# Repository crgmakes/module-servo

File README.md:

# Servo Module

All the source files for the servo module hardware.

# Software 

You will need [KiCad](https://kicad.org) to view and edit this design. Click [here](https://www.kicad.org/download/) to download.

You will also need all the associated libraries and models to drive the design if you want to make changes or view the 3D rendering:

https://github.com/crgmakes/kicad-library.git

Kicad MUST be configured properly to use all the files in this repo. Once you have Kicad installed, under Preferences->Configure Paths..., make the following entries:

1. KICAD_USER_DIR -> set to the root location of where you placed the above repository.
2. KICAD_USER_LIBRARY = ${KICAD_USER_DIR}/Library
3. KICAD_USER_MODEL_DIR = ${KICAD_USER_LIBRARY}/models
4. KICAD_USER_TEMPLATE_DIR = ${KICAD_USER_LIBRARY}/templates	

Kicad will operate mostly normally if these are not set properly. You will notice an issue when you view the PCB in 3D mode.

***NOTE***: after makeing a release build in git, if your rendered 3D images are missing components, ensure the path to EVERY component model is set to ${KICAD_USER_MODEL_DIR}/<model name>.

Kicad sometimes replaces the variable with an expansion and that FAILS during the build process because the expanded variable is local and does not match the build environment.

---

THE DESIGN IS PROVIDED "AS IS" AND THE AUTHOR DISCLAIMS ALL WARRANTIES WITH REGARD TO THIS DESIGN INCLUDING ALL IMPLIED WARRANTIES OF MERCHANTABILITY AND FITNESS. IN NO EVENT SHALL THE AUTHOR BE LIABLE FOR ANY SPECIAL, DIRECT, INDIRECT, OR CONSEQUENTIAL DAMAGES OR ANY DAMAGES WHATSOEVER RESULTING FROM LOSS OF USE, DATA OR PROFITS, WHETHER IN AN ACTION OF CONTRACT, NEGLIGENCE OR OTHER TORTIOUS ACTION, ARISING OUT OF OR IN CONNECTION WITH THE USE OR PERFORMANCE OF THIS DESIGN.

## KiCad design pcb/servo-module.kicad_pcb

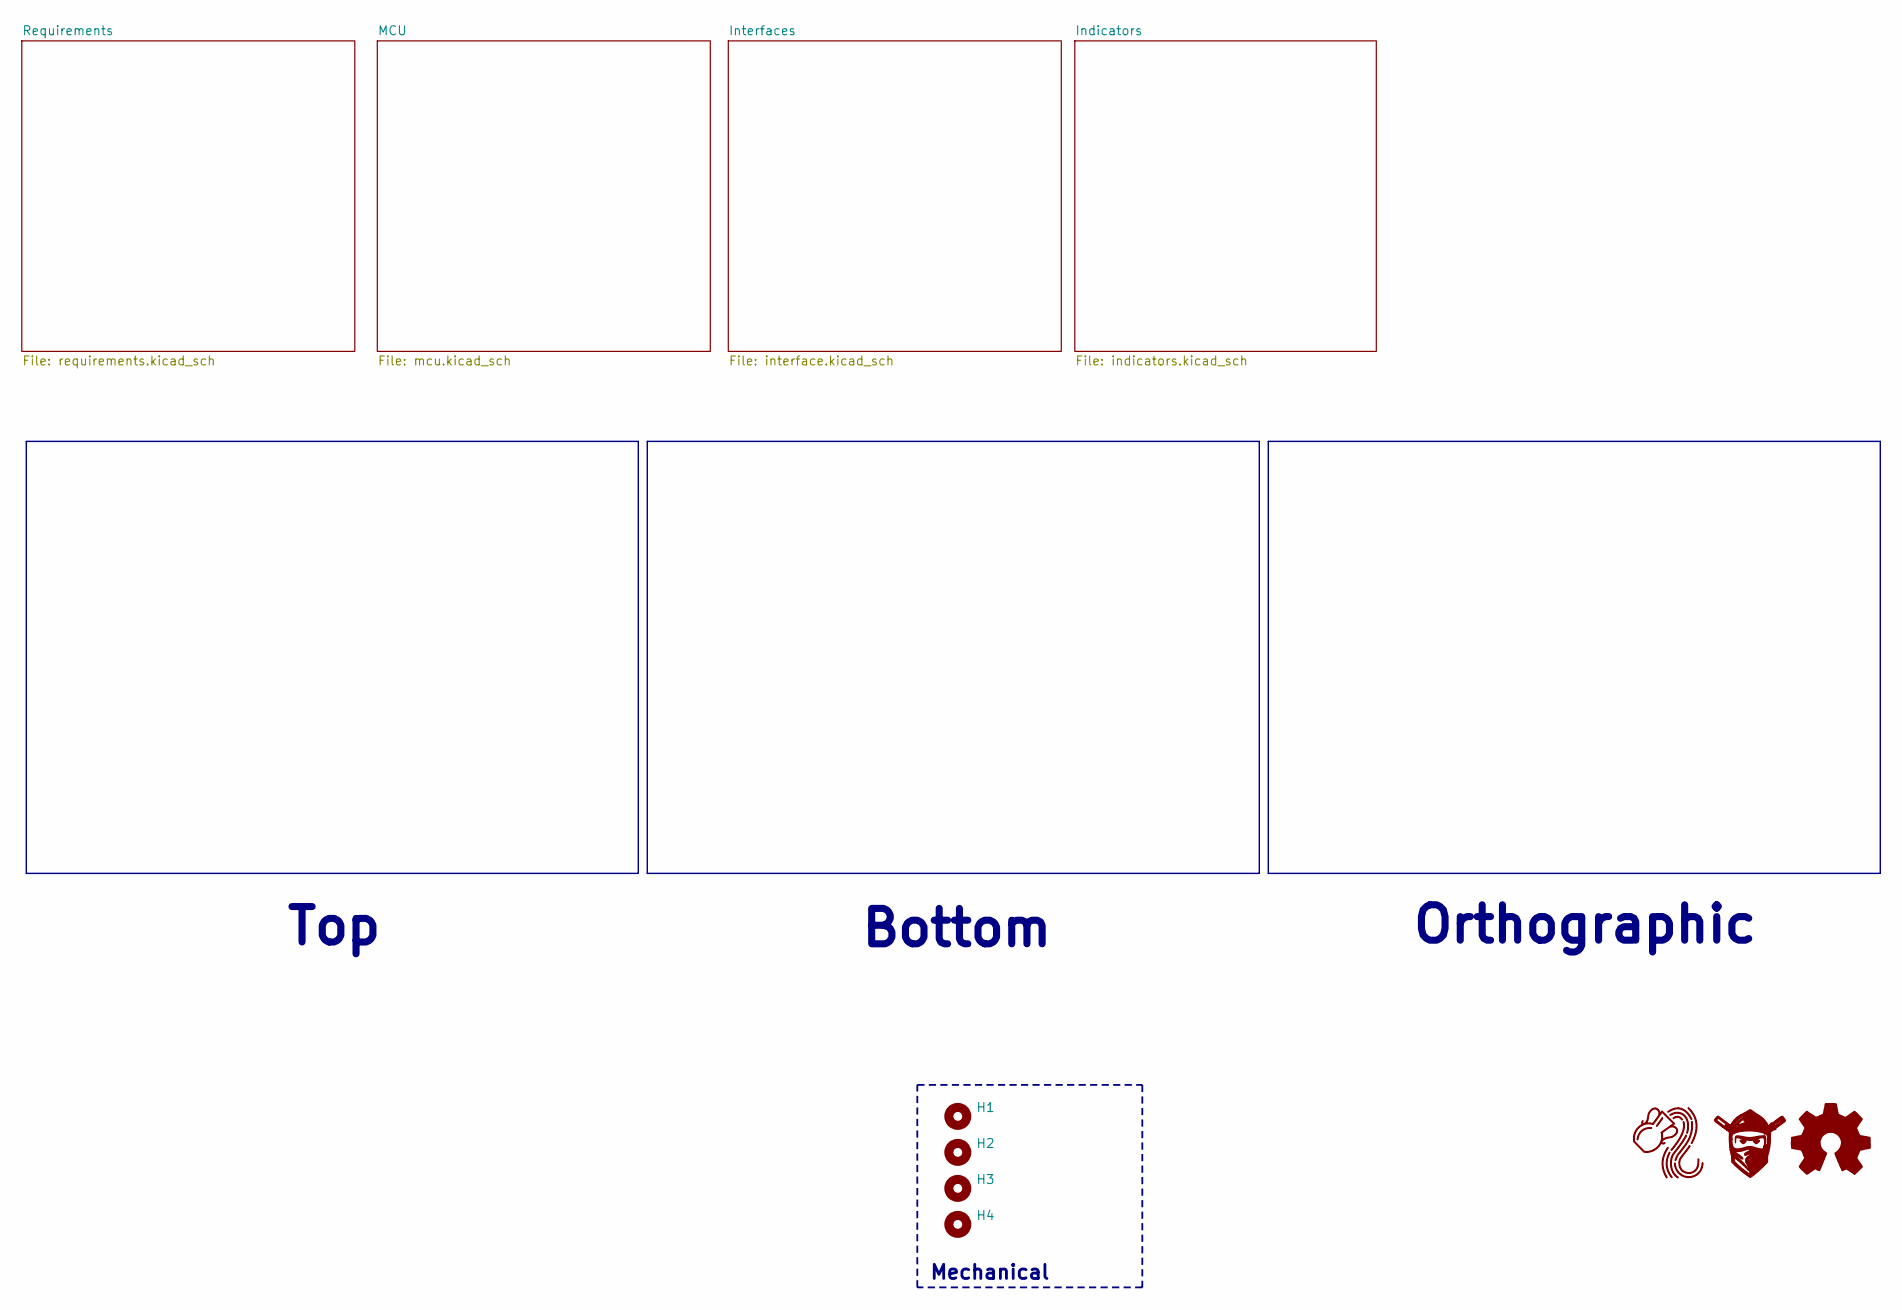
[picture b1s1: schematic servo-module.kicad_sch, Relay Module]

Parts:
H1, H2, H3, H4: MountingHole; MountingHole_3.2mm_M3_Pad_Via
LOGO1: Aquarius Logo 8mm
LOGO2: FNWW Face 8mm
LOGO3: Logo_Open_Hardware_Small; OSHW-Logo_5.7x6mm_SilkScreen

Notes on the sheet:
Mechanical
Bottom
Orthographic
Top

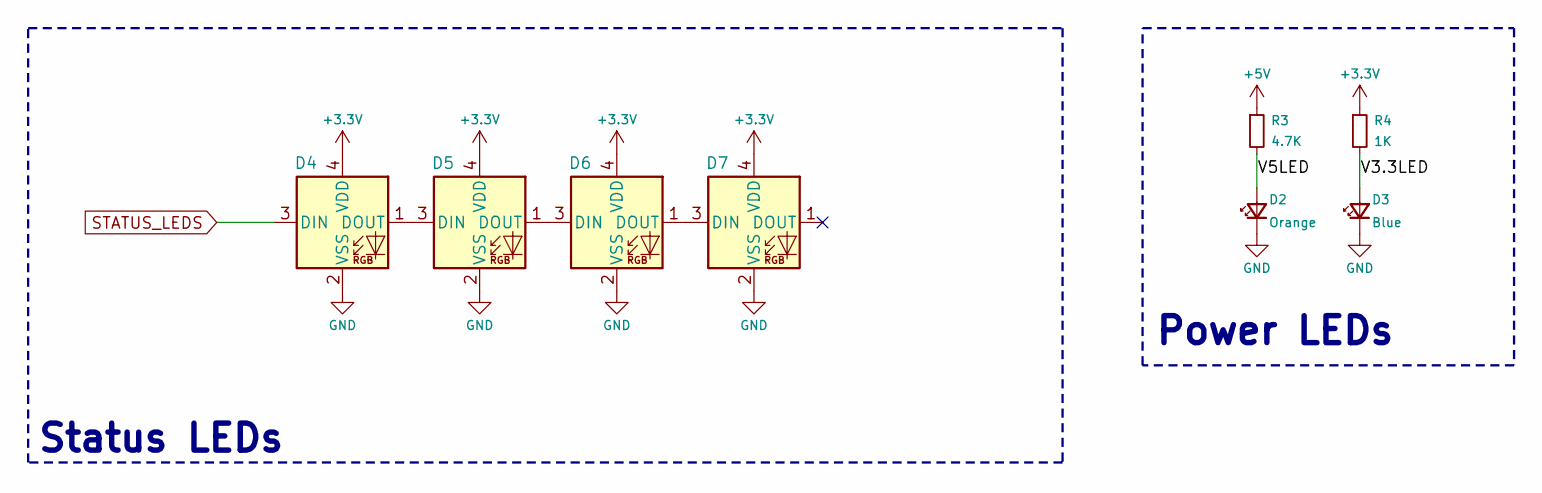
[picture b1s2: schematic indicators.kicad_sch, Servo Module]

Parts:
D2: Orange; LED_0603_1608Metric; MPN XL-1608UOC-06; Mouser 859-LTST-C190KFKT
D3: Blue; LED_0603_1608Metric; MPN XL-1608UBC-04; Mouser 710-150060BS75020
D4, D5, D6, D7: WS2812B-2020; LED_WS2812B-2020_PLCC4_2.0x2.0mm; MPN WS2812C-2020-V1; LCSC C2976072
R3: 4.7K; R_0603_1608Metric; MPN FRC0603J472 TS; Mouser 71-CRCW06034K70JNEAC
R4: 1K; R_0603_1608Metric; MPN CRCW06031K00FKEA; Mouser 71-CRCW06031K00JNEAC

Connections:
+3.3V: D4.4 (VDD), D5.4 (VDD), D6.4 (VDD), D7.4 (VDD), R4.1; also elsewhere on the board
+5V: R3.1; also elsewhere on the board
/Indicators/V3.3LED: D3.2 (A), R4.2
/Indicators/V5LED: D2.2 (A), R3.2
GND: D2.1 (K), D3.1 (K), D4.2 (VSS), D5.2 (VSS), D6.2 (VSS), D7.2 (VSS); also elsewhere on the board
unnamed: D4.1 (DOUT), D5.3 (DIN)
unnamed: D5.1 (DOUT), D6.3 (DIN)
unnamed: D6.1 (DOUT), D7.3 (DIN)
STATUS_LEDS: D4.3 (DIN); also elsewhere on the board

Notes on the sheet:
Status LEDs
Power LEDs

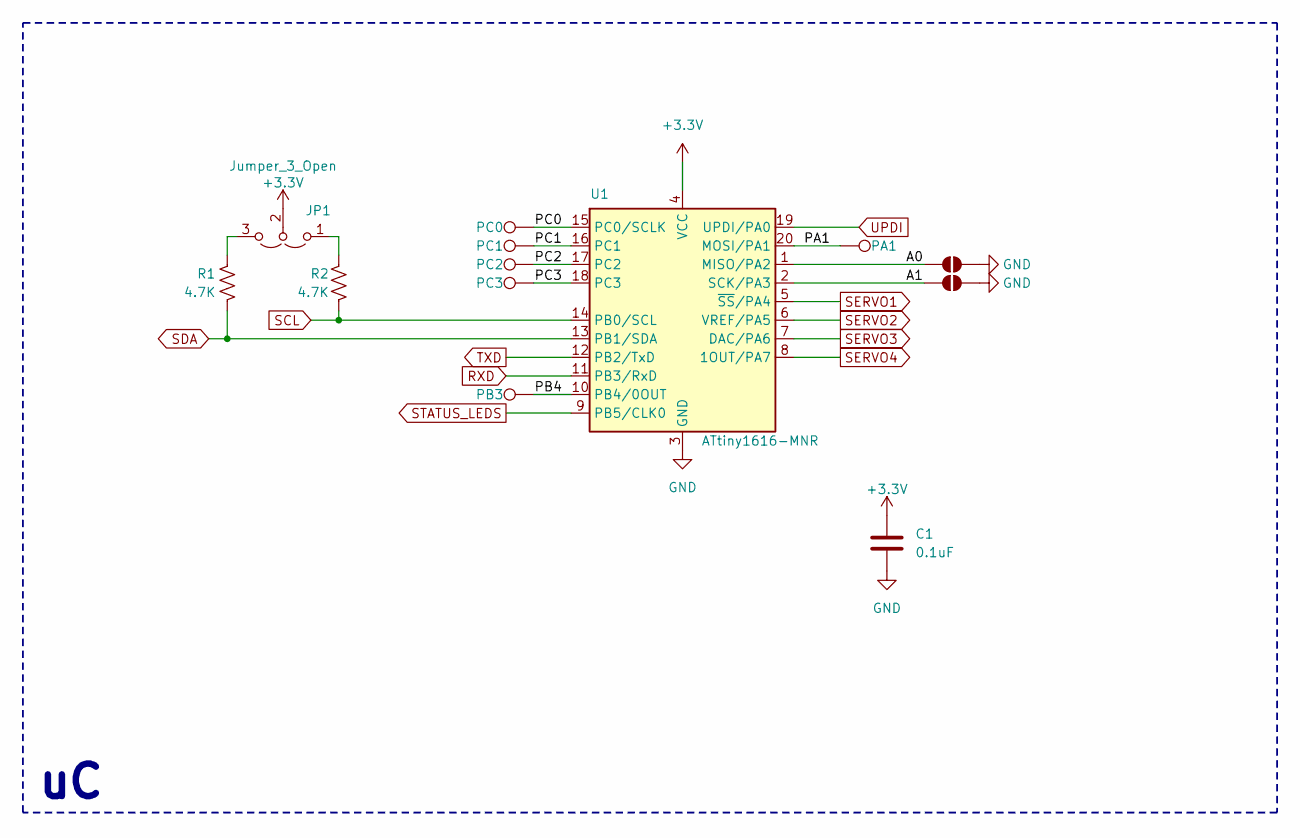
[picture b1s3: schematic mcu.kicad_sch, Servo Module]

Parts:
C1: 0.1uF; C_0603_1608Metric; MPN CL10A105KB8NNNC; LCSC C15849
JP1: Jumper_3_Open; SolderJumper-3_P1.3mm_Open_RoundedPad1.0x1.5mm
JP2: A0; SolderJumper-2_P1.3mm_Open_RoundedPad1.0x1.5mm
JP3: A1; SolderJumper-2_P1.3mm_Open_RoundedPad1.0x1.5mm
R1: 4.7K; R_0603_1608Metric; MPN FRC0603J472 TS; Mouser 71-CRCW06034K70JNEAC
R2: 4.7K; R_0603_1608Metric; MPN FRC0603J472 TS; LCSC C2907166
TP1: PA1; TestPoint_Pad_D1.0mm
TP2: PC0; TestPoint_Pad_D1.0mm
TP3: PC1; TestPoint_Pad_D1.0mm
TP13: PB3; TestPoint_Pad_D1.0mm
TP14: PC3; TestPoint_Pad_D1.0mm
TP15: PC2; TestPoint_Pad_D1.0mm
U1: ATtiny1616-MNR; VQFN-20-1EP_3x3mm_P0.4mm_EP1.7x1.7mm_ThermalVias; MPN ATTINY1616-MNR; Mouser 556-ATTINY1616MNR

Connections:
+3.3V: C1.1, JP1.2 (C), U1.4 (VCC); also elsewhere on the board
/MCU/A0: JP2.2 (B), U1.1 (MISO/PA2)
/MCU/A1: JP3.2 (B), U1.2 (SCK/PA3)
/MCU/PA1: TP1.1, U1.20 (MOSI/PA1)
/MCU/PB4: TP13.1, U1.10 (PB4/0OUT)
/MCU/PC0: TP2.1, U1.15 (PC0/SCLK)
/MCU/PC1: TP3.1, U1.16 (PC1)
/MCU/PC2: TP15.1, U1.17 (PC2)
/MCU/PC3: TP14.1, U1.18 (PC3)
GND: C1.2, JP2.1 (A), JP3.1 (A), U1.3 (GND), U1.21 (GND); also elsewhere on the board
unnamed: JP1.1 (A), R2.2
unnamed: JP1.3 (B), R1.2
RXD: U1.11 (PB3/RxD); also elsewhere on the board
SCL: R2.1, U1.14 (PB0/SCL); also elsewhere on the board
SDA: R1.1, U1.13 (PB1/SDA); also elsewhere on the board
SERVO1: U1.5 (~SS/PA4); also elsewhere on the board
SERVO2: U1.6 (VREF/PA5); also elsewhere on the board
SERVO3: U1.7 (DAC/PA6); also elsewhere on the board
SERVO4: U1.8 (1OUT/PA7); also elsewhere on the board
STATUS_LEDS: U1.9 (PB5/CLK0); also elsewhere on the board
TXD: U1.12 (PB2/TxD); also elsewhere on the board
UPDI: U1.19 (UPDI/PA0); also elsewhere on the board

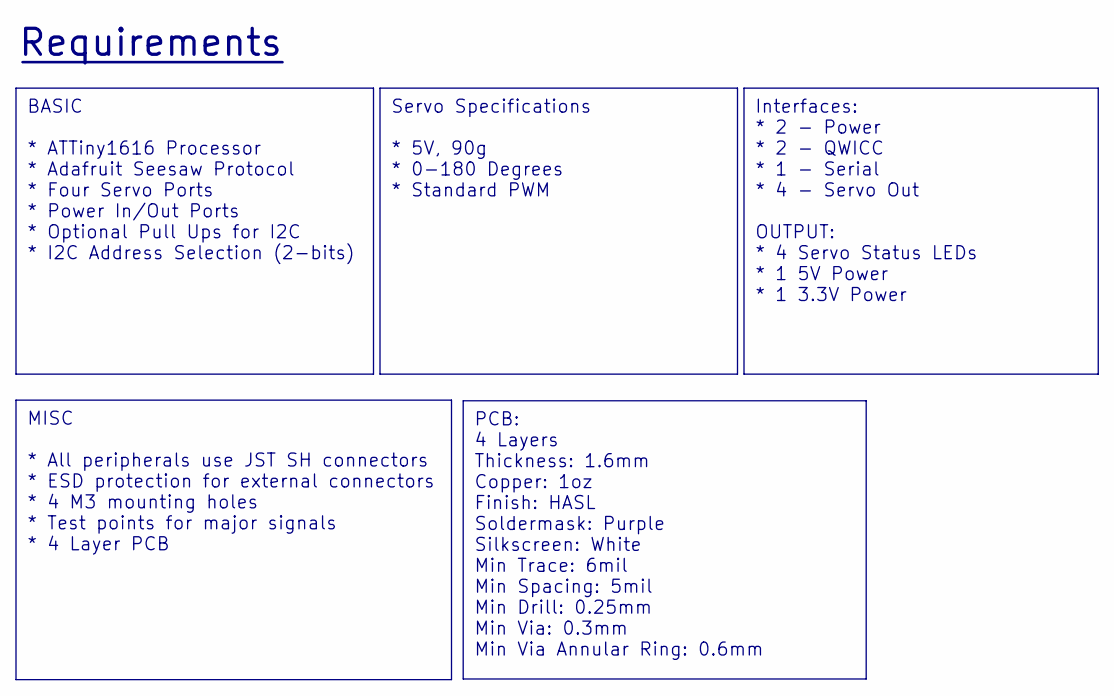
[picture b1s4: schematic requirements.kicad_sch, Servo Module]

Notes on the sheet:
Requirements
PCB: 4 Layers Thickness: 1.6mm Copper: 1oz Finish: HASL Soldermask: Purple Silkscreen: White Min Trace: 6mil Min Spacing: 5mil Min Drill: 0.25mm Min Via: 0.3mm Min Via Annular Ring: 0.6mm
BASIC * ATTiny1616 Processor * Adafruit Seesaw Protocol * Four Servo Ports * Power In/Out Ports * Optional Pull Ups for I2C * I2C Address Selection (2-bits)
Interfaces: * 2 - Power * 2 - QWICC * 1 - Serial * 4 - Servo Out OUTPUT: * 4 Servo Status LEDs * 1 5V Power * 1 3.3V Power
MISC * All peripherals use JST SH connectors * ESD protection for external connectors * 4 M3 mounting holes * Test points for major signals * 4 Layer PCB
Servo Specifications * 5V, 90g * 0-180 Degrees * Standard PWM

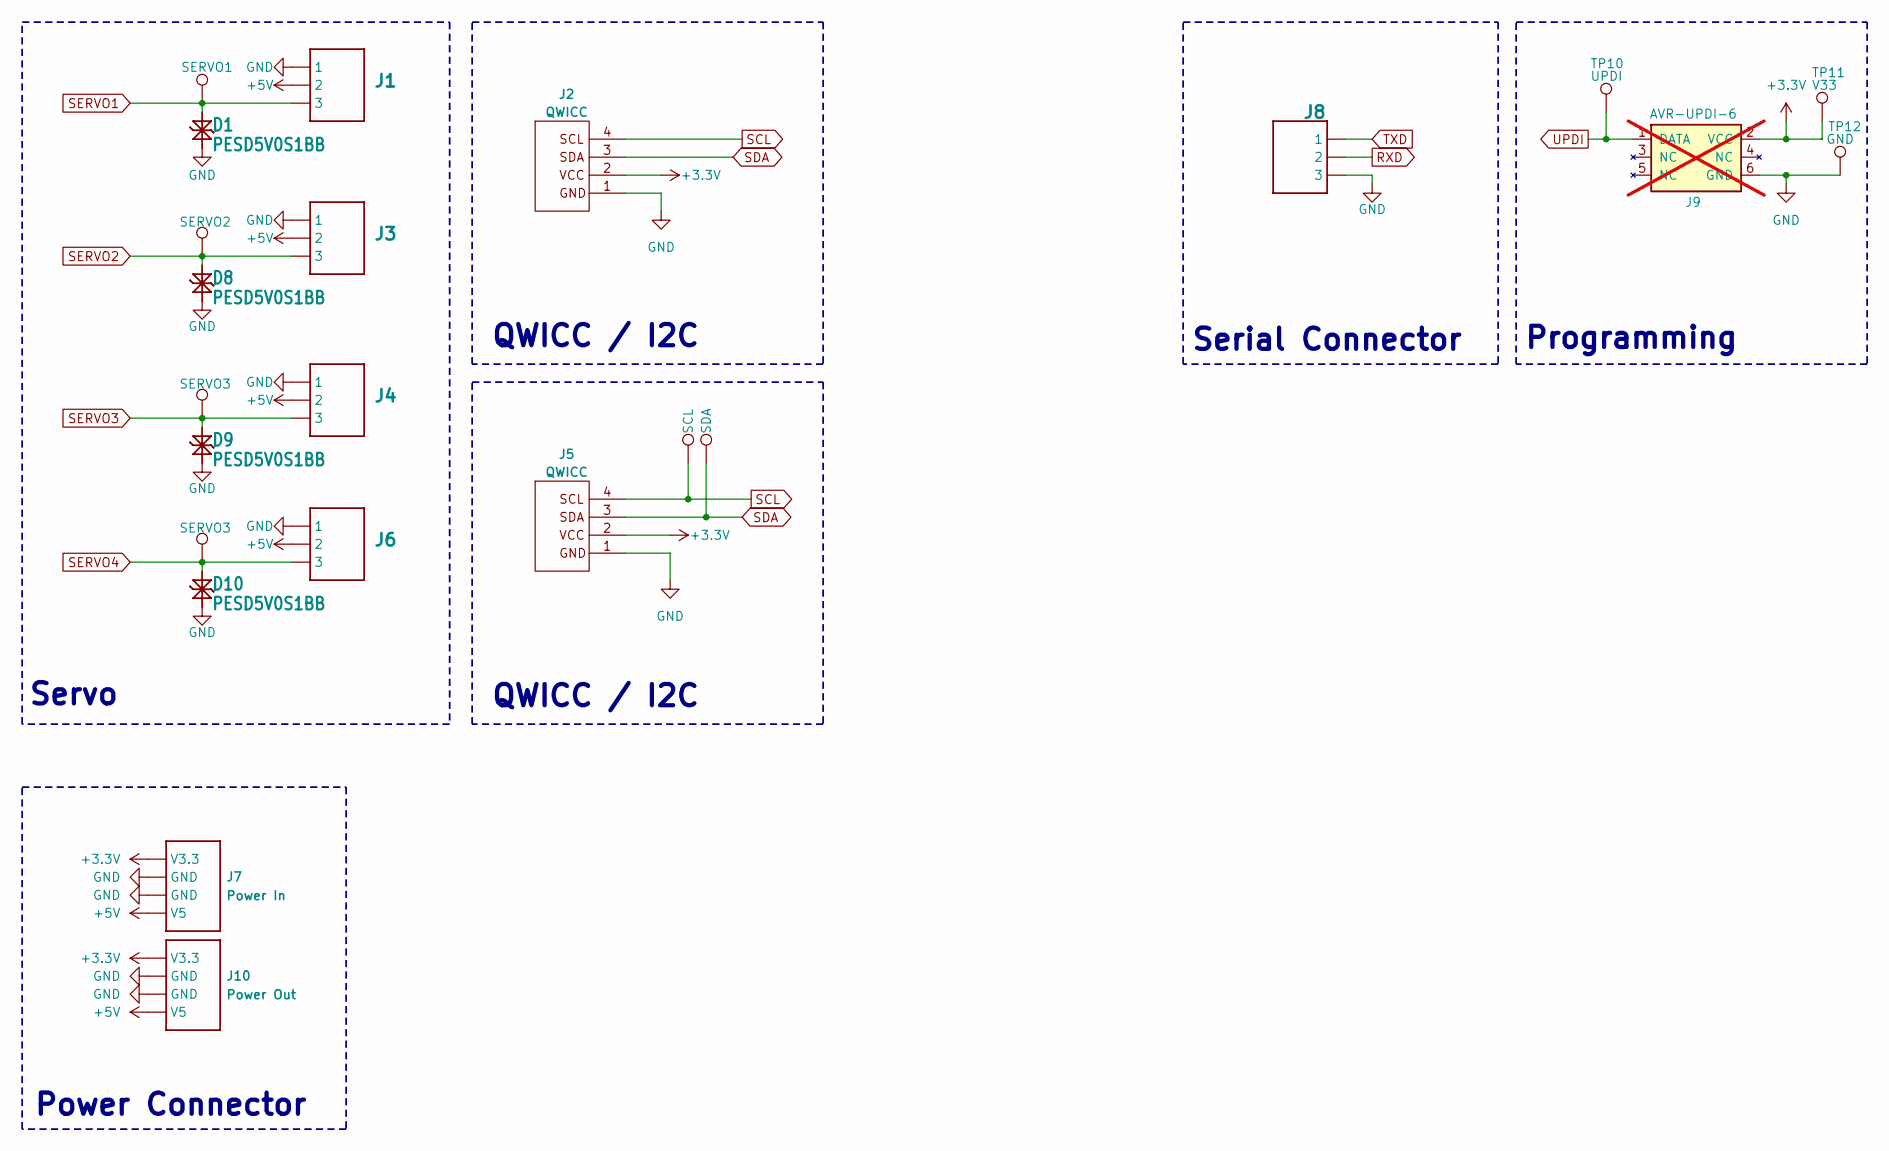
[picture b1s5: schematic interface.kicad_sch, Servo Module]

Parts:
D1, D8, D9, D10: PESD5V0S1BB; D_SOD-523; MPN PESD5V0S1BB,115; LCSC C314264
J1, J3, J4, J6, J8: JST_SH_BM03B-SRSS-TB_1x03-1MP_P1.00mm_Vertical; MPN BM03B-SRSS-TB; Mouser 306-BM03BSRSSTBLFSNP
J2, J5: QWICC; JST_SH_SM04B-SRSS-TB_1x04-1MP_P1.00mm_Horizontal; MPN SM04B-SRSS-TBT(LF)(SN); Mouser 306-SM04BSRSSTBTLFSN
J7: Power In; JST_SH_SM04B-SRSS-TB_1x04-1MP_P1.00mm_Horizontal; MPN SM04B-SRSS-TBT(LF)(SN); Mouser 306-SM04BSRSSTBTLFSN
J9: AVR-UPDI-6; PinHeader_2x03_P2.54mm_Vertical_SMD; not fitted
J10: Power Out; JST_SH_SM04B-SRSS-TB_1x04-1MP_P1.00mm_Horizontal; MPN SM04B-SRSS-TBT(LF)(SN); Mouser 306-SM04BSRSSTBTLFSN
TP4: SERVO1; TestPoint_Pad_D1.0mm
TP5: SERVO2; TestPoint_Pad_D1.0mm
TP6, TP9: SERVO3; TestPoint_Pad_D1.0mm
TP7: SCL; TestPoint_Pad_D1.0mm
TP8: SDA; TestPoint_Pad_D1.0mm
TP10: UPDI; TestPoint_Pad_D1.0mm
TP11: V33; TestPoint_Pad_D1.0mm
TP12: GND; TestPoint_Pad_D1.0mm

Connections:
+3.3V: J2.2, J5.2, J7.4 (V3.3), J9.2 (VCC), J10.4 (V3.3), TP11.1; also elsewhere on the board
+5V: J1.2, J3.2, J4.2, J6.2, J7.1 (V5), J10.1 (V5); also elsewhere on the board
GND: D1.1 (K1), D8.1 (K1), D9.1 (K1), D10.1 (K1), J1.1, J2.1, J3.1, J4.1, J5.1, J6.1, J7.2 (GND), J7.3 (GND), J8.3, J9.6 (GND), J10.2 (GND), J10.3 (GND), TP12.1; also elsewhere on the board
RXD: J8.2; also elsewhere on the board
SCL: J2.4, J5.4, TP7.1; also elsewhere on the board
SDA: J2.3, J5.3, TP8.1; also elsewhere on the board
SERVO1: D1.2 (K2), J1.3, TP4.1; also elsewhere on the board
SERVO2: D8.2 (K2), J3.3, TP5.1; also elsewhere on the board
SERVO3: D9.2 (K2), J4.3, TP6.1; also elsewhere on the board
SERVO4: D10.2 (K2), J6.3, TP9.1; also elsewhere on the board
TXD: J8.1; also elsewhere on the board
UPDI: J9.1 (DATA), TP10.1; also elsewhere on the board

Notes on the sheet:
Programming
Serial Connector
Power Connector
QWICC / I2C
Servo

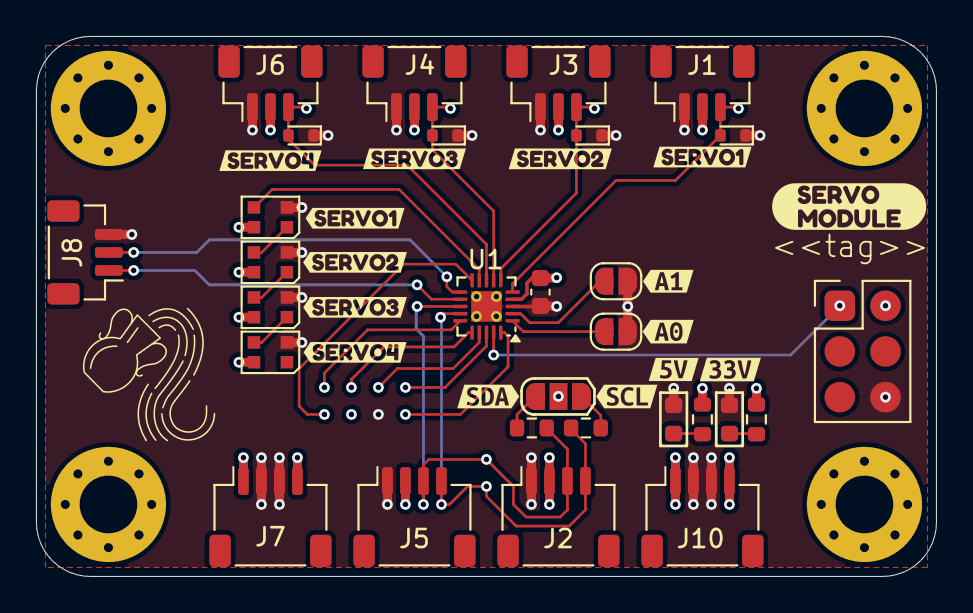
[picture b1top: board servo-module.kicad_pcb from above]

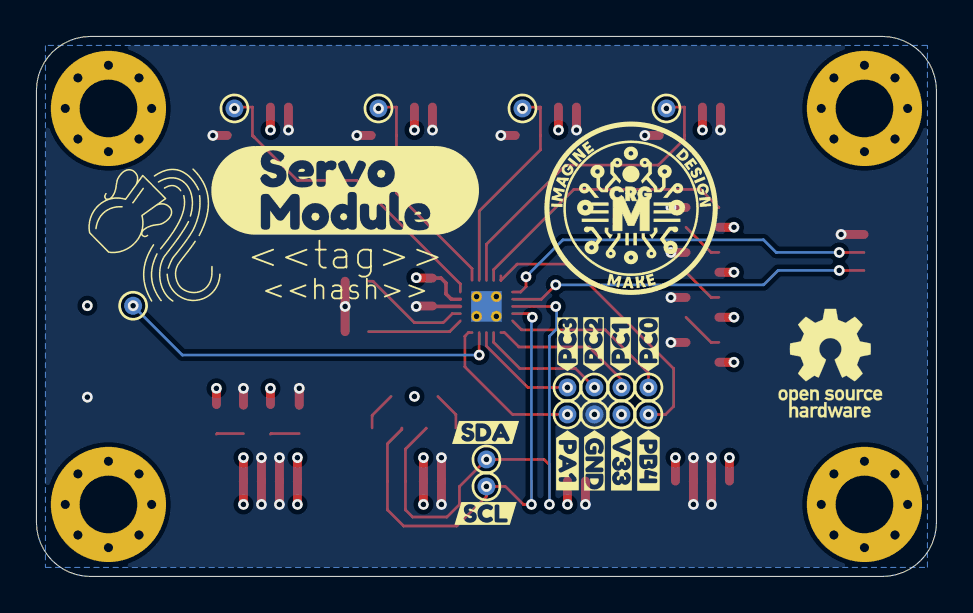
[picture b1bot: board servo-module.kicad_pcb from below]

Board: 4 copper layers, 50.0 x 30.0 mm, 78 parts (29 on the bottom side), 28 nets.

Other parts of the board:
LOGO4: CRGM Logo 5mm
kibuzzard-6861B7EA: G***; kibuzzard-6861B7EA
kibuzzard-6861B80B: G***; kibuzzard-6861B80B
kibuzzard-6861B833: G***; kibuzzard-6861B833
kibuzzard-6861B880: G***; kibuzzard-6861B880
kibuzzard-6861B899: G***; kibuzzard-6861B899
kibuzzard-6862CEAB: G***; kibuzzard-6862CEAB
kibuzzard-6862CEB9: G***; kibuzzard-6862CEB9
kibuzzard-6862CEC0: G***; kibuzzard-6862CEC0
kibuzzard-6862CEE4: G***; kibuzzard-6862CEE4
kibuzzard-68583EA9: G***; kibuzzard-68583EA9
kibuzzard-68583EC3: G***; kibuzzard-68583EC3
kibuzzard-68583EE4: G***; kibuzzard-68583EE4
kibuzzard-68583EEB: G***; kibuzzard-68583EEB
kibuzzard-68583F01: G***; kibuzzard-68583F01
kibuzzard-68583F18: G***; kibuzzard-68583F18
kibuzzard-68583F22: G***; kibuzzard-68583F22
kibuzzard-68583F28: G***; kibuzzard-68583F28
kibuzzard-68585AB3: G***; kibuzzard-68585AB3
kibuzzard-68585C25: G***; kibuzzard-68585C25
kibuzzard-685845A0: G***; kibuzzard-685845A0
kibuzzard-685845CF: G***; kibuzzard-685845CF
kibuzzard-685845E1: G***; kibuzzard-685845E1
kibuzzard-6858441E: G***; kibuzzard-6858441E
kibuzzard-6858446E: G***; kibuzzard-6858446E
kibuzzard-68584599: G***; kibuzzard-68584599
kibuzzard-68586251: G***; kibuzzard-68586251

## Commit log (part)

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2025-03-26 initial check in
2025-03-27 added connectors
2025-04-01 Added additional suppliers and changed some footprints for DRC
2025-04-11 Updated silkscreen
2025-06-23 Made multi-sheet; changed LEDs to WS2812; rerouted whole board
2025-06-23 Added CI scripts
2025-06-26 Updated frame template
2025-06-27 Updated worksheet template
2025-06-27 Updated worksheet template and logo
2025-06-27 Updated CI script
2025-06-29 Updated CI to reuse generic script
2025-06-30 Standardized parts; fixed title box
2025-06-30 Added panel options; moved PCB
2025-07-01 changed vspace to 2mm from 8mm
2025-07-13 Remove relay module schematic and update files
    Deleted pcb/relay.kicad_sch and updated .gitignore to include BOM, rendered output, and FreeCAD backup files. Updated LICENSE.md to clarify KiCAD library location; modified other KiCAD schematic and 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
2025-07-24 Updated license
2025-10-26 Updated .gitignore
2025-11-04 Fixed git scripts
2025-11-05 Reworked based on new standards
    Decreased to 3 servo ports
2025-11-07 clean up and final processing
2025-11-07 Fixed connector to be horizontal
2025-11-16 Updated for DFM
    Added renders to schematic
    Deleted indicators as necessary
    Cleaned up silkscreen
2025-11-17 Updated footprints
2025-11-22 Changed panel to be 2x1
2025-11-22 Updated origin
2025-12-31 Added status leds
    forced to reroute entire board
2026-01-01 Added servo power and filtering
    Added connection for servo power
    Added solder jumper for servo power to 5V
    Added caps to servo power
    Added bulk decoupling caps
    Added TVS to various inputs
    Updated renders
2026-01-01 Fixed model directory for servo pwr connector
2026-01-18 minor silkscreen change
2026-02-03 Adjusting back on lessons learned from 1.1,
    Added skilkscreen
    Moved UART to UPDI connector
    Created room for 4th servo connector?
2026-02-27 Updated title; deleted unnecessary files
2026-03-01 replaced .wrl with .step
2026-03-22 changed connectors to vertical
    Updated connectors with ground on mounting points
    Updated and rerouted
2026-03-23 Finished routing
    Updated renders
    Added 4th LED
    Fixed LED wiring
2026-06-10 Removed space in MN for resistors
2026-06-10 Updated models
2026-06-10 Updated more models
2026-06-10 Fixed mcu model path
2026-06-13 Redesign with SMT32
    Complete redesign using SMT32 instead of ATTINY.
2026-06-13 Rearranged parts
    Moved cap and power connector for SV power.
    Moved SV PWR LED.
    Moved reset switch.
2026-06-13 Fixed models; adjusted layout
2026-06-14 Moved servo power connector to center
    Updated silkscreen
    Updated renders
    Increased size of Roxy ❤️
2026-06-15 Fixed massive part/bom mismatches.
2026-06-15 removed space
2026-06-15 Fixed PCB Title name
2026-06-16 Updated MN and MPN
2026-06-30 Fixed text and alignment on schematic
